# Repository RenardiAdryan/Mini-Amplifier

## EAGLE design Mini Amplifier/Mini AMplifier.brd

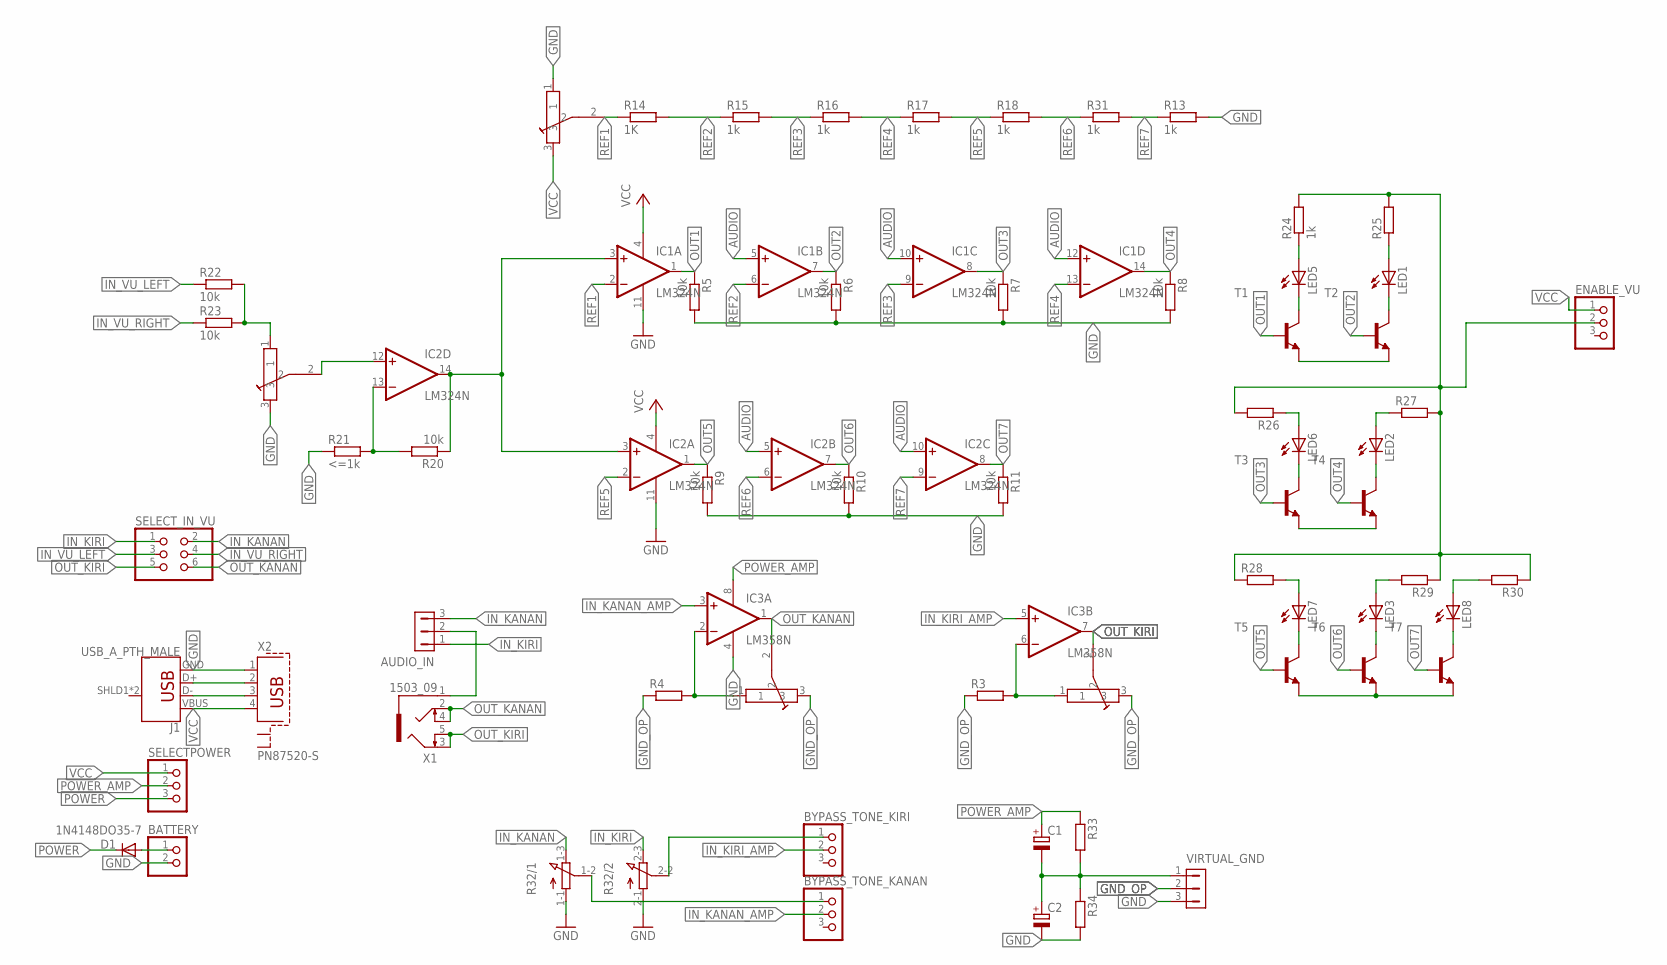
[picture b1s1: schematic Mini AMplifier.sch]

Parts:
AUDIO_IN: HDR-1X3; SIP-100-3V
BATTERY: PINHD-1X2; 1X02
BYPASS_TONE_KANAN: PINHD-1X3; 1X03
BYPASS_TONE_KIRI: PINHD-1X3; 1X03
C1, C2: CPOL-EUE2.5-6; E2,5-6
D1: 1N4148DO35-7; DO35-7
ENABLE_VU: PINHD-1X3; 1X03
IC1, IC2: LM324N; DIL14
IC3: LM358N; DIL08
J1: USB_A_PTH_MALE; USB-A-H
LED1, LED2, LED3, LED5, LED6, LED7, LED8: LED3MM
R3, R4, R25, R26, R27, R28, R29, R30: R; R0805
R5, R6, R7, R8, R9, R10, R11: 10k; 0204/7
R13, R15, R16, R17, R18, R31: 1k; 0204/7
R14: 1K; 0204/7
R20, R22, R23: 10k; R0805
R21: <=1k; R0805
R24: 1k; R0805
R32: 3RP/1610G
R33, R34: R0204/7; 0204/7
SELECTPOWER: PINHD-1X3; 1X03
SELECT_IN_VU: PINHD-2X3; 2X03
T1, T2, T3, T4, T5, T6, T7: -NPN-TO92-EBC; TO92-EBC
U$1, U$2, U$3, U$4: TRIMPOT
VIRTUAL_GND: HDR-1X3; SIP-100-3V
X1: 1503_09
X2: PN87520-S

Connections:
AUDIO: IC1.3 (+IN), IC1.5 (+IN), IC1.10 (+IN), IC1.12 (+IN), IC2.3 (+IN), IC2.5 (+IN), IC2.10 (+IN), IC2.14 (OUT), R20.1
GND: BATTERY.2, C2.-, IC1.11 (V-), IC2.11 (V-), IC3.4 (V-), J1.GND, R5.2, R6.2, R7.2, R8.2, R9.2, R10.2, R11.2, R13.2, R21.1, R32.1-1 (A), R32.2-1 (A), R34.2, T1.E, T2.E, T3.E, T4.E, T5.E, T6.E, T7.E, U$1.3, U$2.1, VIRTUAL_GND.3, X2.1
GND_OP: R3.1, R4.1, U$3.3, U$4.3, VIRTUAL_GND.2
IN_KANAN: AUDIO_IN.3, R32.1-3 (E), SELECT_IN_VU.2
IN_KANAN_AMP: BYPASS_TONE_KANAN.2, IC3.3 (+IN)
IN_KIRI: AUDIO_IN.1, R32.2-3 (E), SELECT_IN_VU.1
IN_KIRI_AMP: BYPASS_TONE_KIRI.2, IC3.5 (+IN)
IN_VU_LEFT: R22.1, SELECT_IN_VU.3
IN_VU_RIGHT: R23.1, SELECT_IN_VU.4
LAMPU: ENABLE_VU.2, R24.2, R25.2, R26.2, R27.2, R28.1, R29.1, R30.1
unnamed: AUDIO_IN.2, X1.1
unnamed: LED5.K (C), T1.C
unnamed: IC3.6 (-IN), R3.2, U$4.1
unnamed: IC3.2 (-IN), R4.2, U$3.1
unnamed: LED1.K (C), T2.C
unnamed: IC2.12 (+IN), U$1.2
unnamed: LED6.K (C), T3.C
unnamed: LED2.K (C), T4.C
unnamed: IC2.13 (-IN), R20.2, R21.2
unnamed: LED7.A, R28.2
unnamed: LED3.K (C), T6.C
unnamed: LED7.K (C), T5.C
unnamed: LED8.K (C), T7.C
unnamed: R22.2, R23.2, U$1.1
unnamed: LED3.A, R29.2
unnamed: LED8.A, R30.2
unnamed: LED6.A, R26.1
unnamed: LED2.A, R27.1
unnamed: LED5.A, R24.1
unnamed: LED1.A, R25.1
unnamed: BATTERY.1, D1.A
unnamed: J1.D+, X2.2
unnamed: J1.D-, X2.3
unnamed: C1.-, C2.+, R33.2, R34.1, VIRTUAL_GND.1
unnamed: BYPASS_TONE_KANAN.1, R32.1-2 (S)
unnamed: BYPASS_TONE_KIRI.1, R32.2-2 (S)
OUT1: IC1.1 (OUT), R5.1, T1.B
OUT2: IC1.7 (OUT), R6.1, T2.B
OUT3: IC1.8 (OUT), R7.1, T3.B
OUT4: IC1.14 (OUT), R8.1, T4.B
OUT5: IC2.1 (OUT), R9.1, T5.B
OUT6: IC2.7 (OUT), R10.1, T6.B
OUT7: IC2.8 (OUT), R11.1, T7.B
OUT_KANAN: IC3.1 (OUT), SELECT_IN_VU.6, U$3.2, X1.2, X1.4
OUT_KIRI: IC3.7 (OUT), SELECT_IN_VU.5, U$4.2, X1.3, X1.5
POWER: D1.C, SELECTPOWER.3
POWER_AMP: C1.+, IC3.8 (V+), R33.1, SELECTPOWER.2
REF1: IC1.2 (-IN), R14.1, U$2.2
REF2: IC1.6 (-IN), R14.2, R15.1
REF3: IC1.9 (-IN), R15.2, R16.1
REF4: IC1.13 (-IN), R16.2, R17.1
REF5: IC2.2 (-IN), R17.2, R18.1
REF6: IC2.6 (-IN), R18.2, R31.1
REF7: IC2.9 (-IN), R13.1, R31.2
VCC: ENABLE_VU.1, IC1.4 (V+), IC2.4 (V+), J1.VBUS, SELECTPOWER.1, U$2.3, X2.4

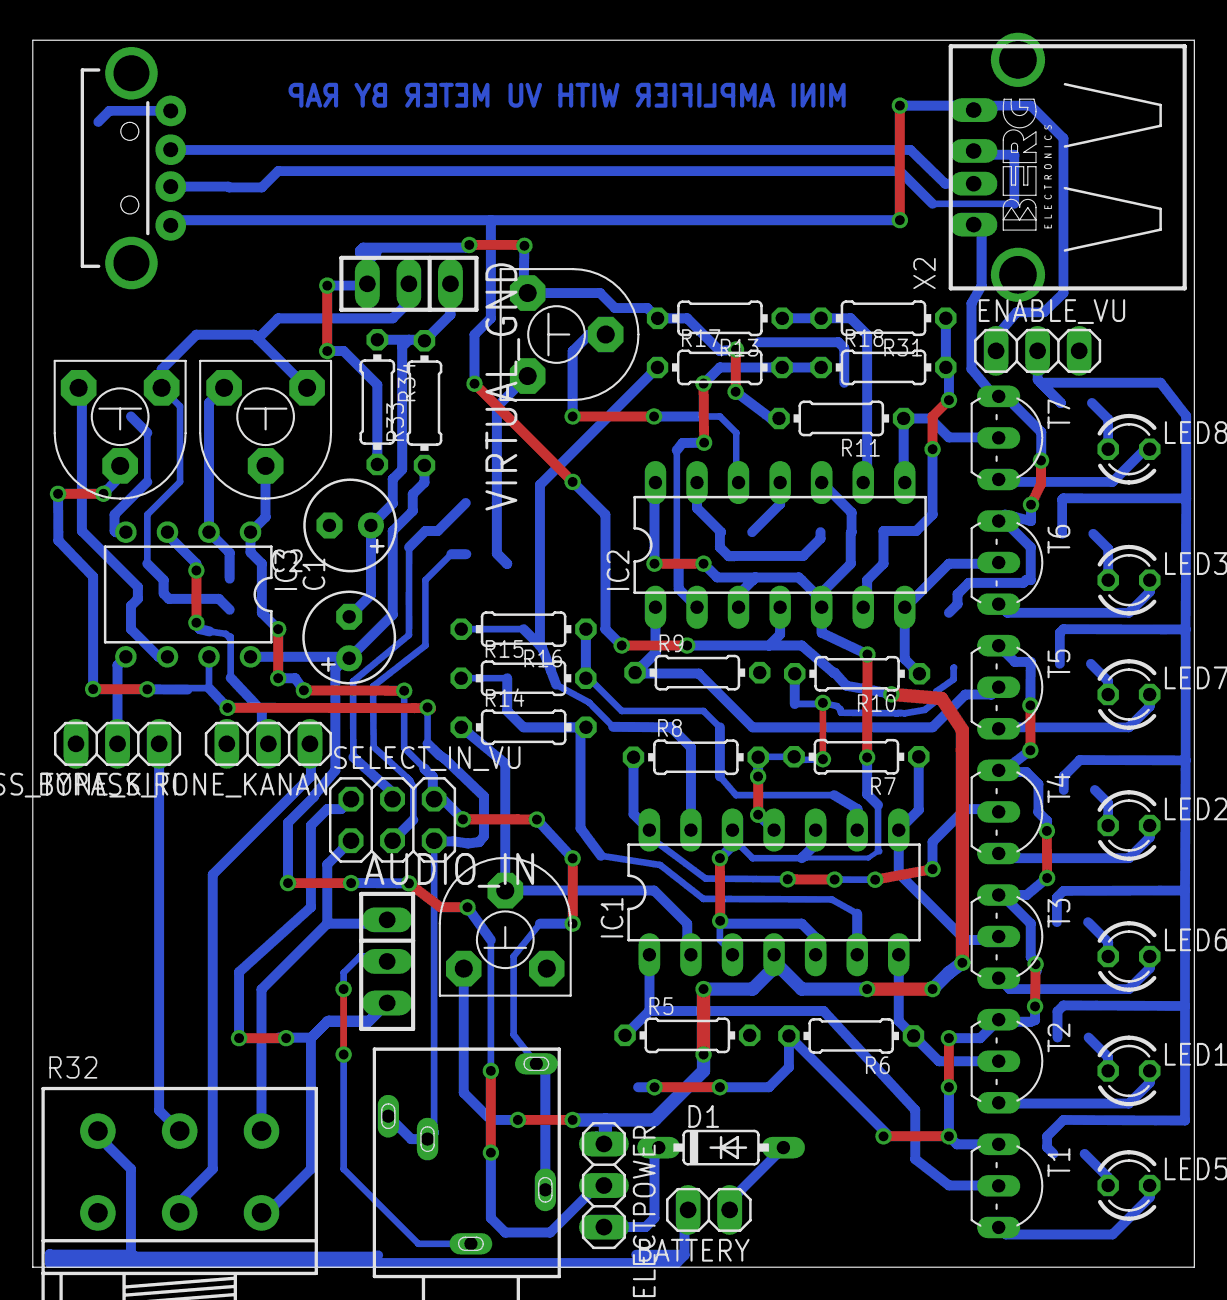
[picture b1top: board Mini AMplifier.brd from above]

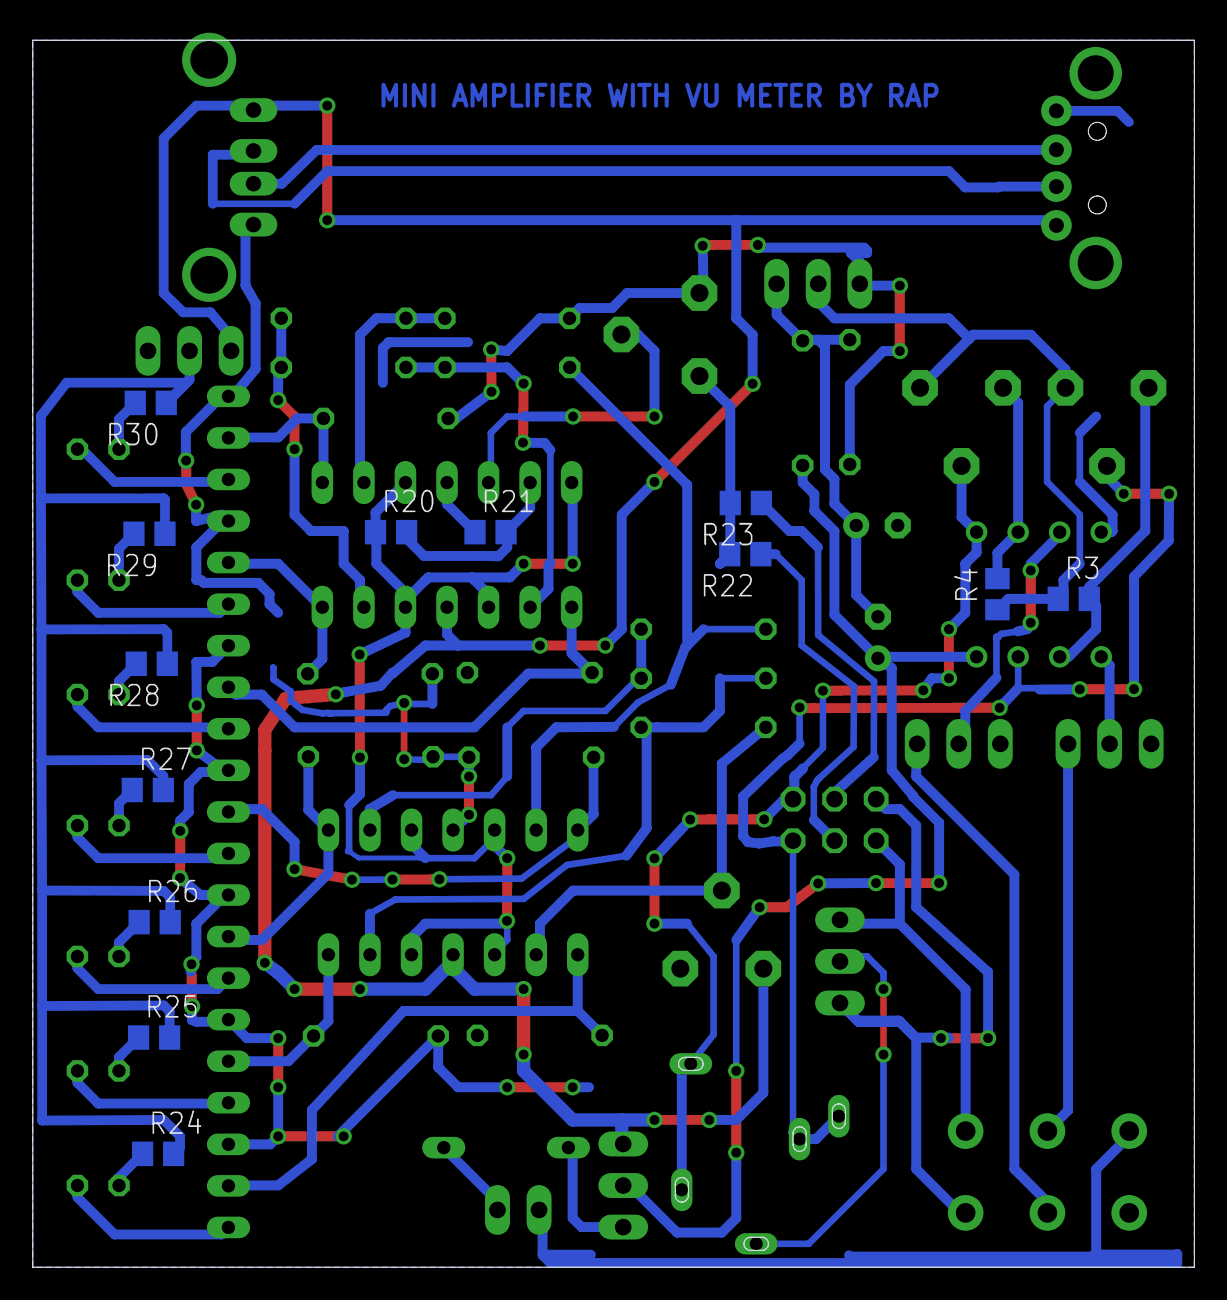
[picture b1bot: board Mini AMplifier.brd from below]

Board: 2 copper layers, 71.0 x 75.0 mm, 65 parts (13 on the bottom side), 55 nets.

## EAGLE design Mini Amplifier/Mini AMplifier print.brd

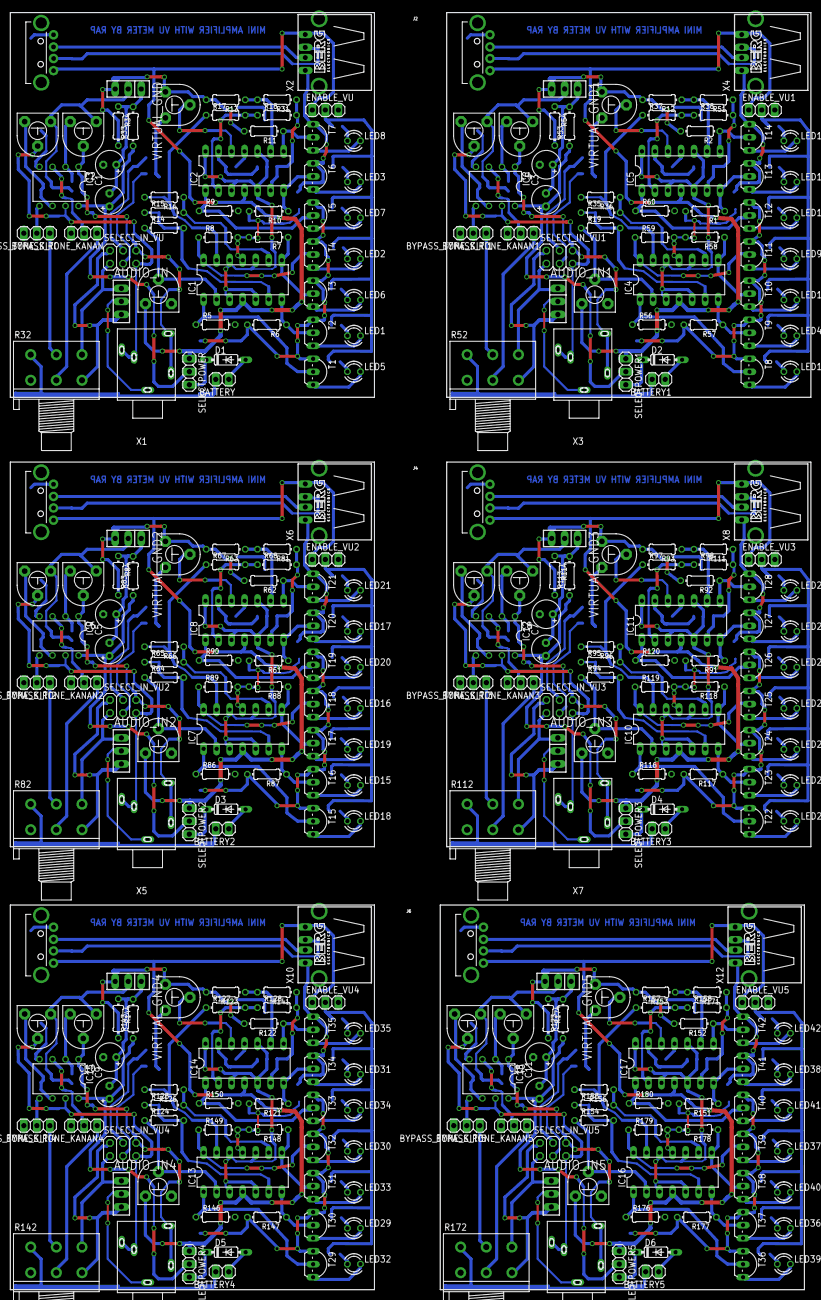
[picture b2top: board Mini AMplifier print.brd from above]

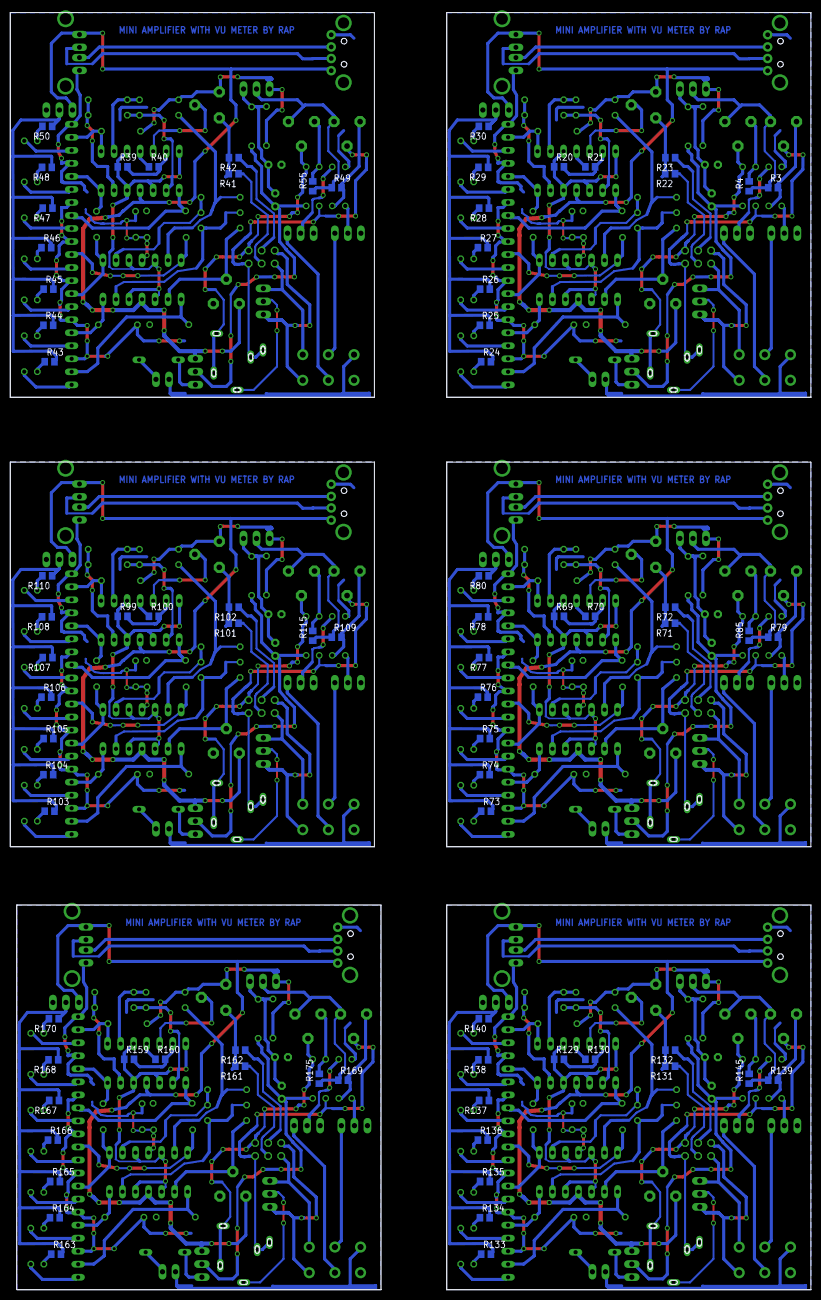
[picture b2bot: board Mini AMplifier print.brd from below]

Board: 2 copper layers, 156.1 x 249.0 mm, 390 parts (78 on the bottom side), 330 nets.

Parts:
AUDIO_IN, AUDIO_IN1, AUDIO_IN2, AUDIO_IN3, AUDIO_IN4, AUDIO_IN5: SIP-100-3V
BATTERY, BATTERY1, BATTERY2, BATTERY3, BATTERY4, BATTERY5: 1X02
BYPASS_TONE_KANAN, BYPASS_TONE_KANAN1, BYPASS_TONE_KANAN2, BYPASS_TONE_KANAN3, BYPASS_TONE_KANAN4, BYPASS_TONE_KANAN5: 1X03
BYPASS_TONE_KIRI, BYPASS_TONE_KIRI1, BYPASS_TONE_KIRI2, BYPASS_TONE_KIRI3, BYPASS_TONE_KIRI4, BYPASS_TONE_KIRI5: 1X03
C1, C2, C3, C4, C5, C6, C7, C8, C9, C10, C11, C12: E2,5-6
D1, D2, D3, D4, D5, D6: 1N4148DO35-7; DO35-7
ENABLE_VU, ENABLE_VU1, ENABLE_VU2, ENABLE_VU3, ENABLE_VU4, ENABLE_VU5: 1X03
IC1, IC2, IC4, IC5, IC7, IC8, IC10, IC11, IC13, IC14, IC16, IC17: LM324N; DIL14
IC3, IC6, IC9, IC12, IC15, IC18: LM358N; DIL08
J1, J2, J3, J4, J5, J6: USB_A_PTH_MALE; USB-A-H
LED1, LED2, LED3, LED4, LED5, LED6, LED7, LED8, LED9, LED10, LED11, LED12, LED13, LED14, LED15, LED16, LED17, LED18, LED19, LED20, LED21, LED22, LED23, LED24, LED25, LED26, LED27, LED28, LED29, LED30, LED31, LED32, LED33, LED34, LED35, LED36, LED37, LED38, LED39, LED40, LED41, LED42: LED3MM
R1, R2, R5, R6, R7, R8, R9, R10, R11, R12, R13, R14, R15, R16, R17, R18, R19, R31, R33, R34, R35, R36, R37, R38, R51, R53, R54, R56, R57, R58, R59, R60, R61, R62, R63, R64, R65, R66, R67, R68, R81, R83, R84, R86, R87, R88, R89, R90, R91, R92, R93, R94, R95, R96, R97, R98, R111, R113, R114, R116, R117, R118, R119, R120, R121, R122, R123, R124, R125, R126, R127, R128, R141, R143, R144, R146, R147, R148, R149, R150, R151, R152, R153, R154, R155, R156, R157, R158, R171, R173, R174, R176, R177, R178, R179, R180: 0204/7
R3, R4, R25, R26, R27, R28, R29, R30, R44, R45, R46, R47, R48, R49, R50, R55, R74, R75, R76, R77, R78, R79, R80, R85, R104, R105, R106, R107, R108, R109, R110, R115, R134, R135, R136, R137, R138, R139, R140, R145, R164, R165, R166, R167, R168, R169, R170, R175: R0805
R20, R22, R23, R39, R41, R42, R69, R71, R72, R99, R101, R102, R129, R131, R132, R159, R161, R162: 10k; R0805
R21, R40, R70, R100, R130, R160: <=1k; R0805
R24, R43, R73, R103, R133, R163: 1k; R0805
R32, R52, R82, R112, R142, R172: 3RP/1610G
SELECTPOWER, SELECTPOWER1, SELECTPOWER2, SELECTPOWER3, SELECTPOWER4, SELECTPOWER5: 1X03
SELECT_IN_VU, SELECT_IN_VU1, SELECT_IN_VU2, SELECT_IN_VU3, SELECT_IN_VU4, SELECT_IN_VU5: 2X03
T1, T2, T3, T4, T5, T6, T7, T8, T9, T10, T11, T12, T13, T14, T15, T16, T17, T18, T19, T20, T21, T22, T23, T24, T25, T26, T27, T28, T29, T30, T31, T32, T33, T34, T35, T36, T37, T38, T39, T40, T41, T42: TO92-EBC
U$1, U$2, U$3, U$4, U$5, U$6, U$7, U$8, U$9, U$10, U$11, U$12, U$13, U$14, U$15, U$16, U$17, U$18, U$19, U$20, U$21, U$22, U$23, U$24: TRIMPOT
VIRTUAL_GND, VIRTUAL_GND1, VIRTUAL_GND2, VIRTUAL_GND3, VIRTUAL_GND4, VIRTUAL_GND5: SIP-100-3V
X1, X3, X5, X7, X9, X11: 1503_09
X2, X4, X6, X8, X10, X12: PN87520-S

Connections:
AUDIO: IC1.3, IC1.5, IC1.10, IC1.12, IC2.3, IC2.5, IC2.10, IC2.14, R20.1
AUDIO1: IC4.3, IC4.5, IC4.10, IC4.12, IC5.3, IC5.5, IC5.10, IC5.14, R39.1
AUDIO2: IC7.3, IC7.5, IC7.10, IC7.12, IC8.3, IC8.5, IC8.10, IC8.14, R69.1
AUDIO3: IC10.3, IC10.5, IC10.10, IC10.12, IC11.3, IC11.5, IC11.10, IC11.14, R99.1
AUDIO4: IC13.3, IC13.5, IC13.10, IC13.12, IC14.3, IC14.5, IC14.10, IC14.14, R129.1
AUDIO5: IC16.3, IC16.5, IC16.10, IC16.12, IC17.3, IC17.5, IC17.10, IC17.14, R159.1
GND: BATTERY.2, C2.-, IC1.11, IC2.11, IC3.4, J1.GND, R5.2, R6.2, R7.2, R8.2, R9.2, R10.2, R11.2, R13.2, R21.1, R32.1-1, R32.2-1, R34.2, T1.E, T2.E, T3.E, T4.E, T5.E, T6.E, T7.E, U$1.3, U$2.1, VIRTUAL_GND.3, X2.1
GND1: BATTERY1.2, C4.-, IC4.11, IC5.11, IC6.4, J2.GND, R1.2, R2.2, R12.2, R40.1, R52.1-1, R52.2-1, R54.2, R56.2, R57.2, R58.2, R59.2, R60.2, T8.E, T9.E, T10.E, T11.E, T12.E, T13.E, T14.E, U$5.3, U$6.1, VIRTUAL_GND1.3, X4.1
GND2: BATTERY2.2, C6.-, IC7.11, IC8.11, IC9.4, J3.GND, R61.2, R62.2, R63.2, R70.1, R82.1-1, R82.2-1, R84.2, R86.2, R87.2, R88.2, R89.2, R90.2, T15.E, T16.E, T17.E, T18.E, T19.E, T20.E, T21.E, U$9.3, U$10.1, VIRTUAL_GND2.3, X6.1
GND3: BATTERY3.2, C8.-, IC10.11, IC11.11, IC12.4, J4.GND, R91.2, R92.2, R93.2, R100.1, R112.1-1, R112.2-1, R114.2, R116.2, R117.2, R118.2, R119.2, R120.2, T22.E, T23.E, T24.E, T25.E, T26.E, T27.E, T28.E, U$13.3, U$14.1, VIRTUAL_GND3.3, X8.1
GND4: BATTERY4.2, C10.-, IC13.11, IC14.11, IC15.4, J5.GND, R121.2, R122.2, R123.2, R130.1, R142.1-1, R142.2-1, R144.2, R146.2, R147.2, R148.2, R149.2, R150.2, T29.E, T30.E, T31.E, T32.E, T33.E, T34.E, T35.E, U$17.3, U$18.1, VIRTUAL_GND4.3, X10.1
GND5: BATTERY5.2, C12.-, IC16.11, IC17.11, IC18.4, J6.GND, R151.2, R152.2, R153.2, R160.1, R172.1-1, R172.2-1, R174.2, R176.2, R177.2, R178.2, R179.2, R180.2, T36.E, T37.E, T38.E, T39.E, T40.E, T41.E, T42.E, U$21.3, U$22.1, VIRTUAL_GND5.3, X12.1
GND_OP: R3.1, R4.1, U$3.3, U$4.3, VIRTUAL_GND.2
GND_OP1: R49.1, R55.1, U$7.3, U$8.3, VIRTUAL_GND1.2
GND_OP2: R79.1, R85.1, U$11.3, U$12.3, VIRTUAL_GND2.2
GND_OP3: R109.1, R115.1, U$15.3, U$16.3, VIRTUAL_GND3.2
GND_OP4: R139.1, R145.1, U$19.3, U$20.3, VIRTUAL_GND4.2
GND_OP5: R169.1, R175.1, U$23.3, U$24.3, VIRTUAL_GND5.2
IN_KANAN: AUDIO_IN.3, R32.1-3, SELECT_IN_VU.2
IN_KANAN1: AUDIO_IN1.3, R52.1-3, SELECT_IN_VU1.2
IN_KANAN2: AUDIO_IN2.3, R82.1-3, SELECT_IN_VU2.2
IN_KANAN3: AUDIO_IN3.3, R112.1-3, SELECT_IN_VU3.2
IN_KANAN4: AUDIO_IN4.3, R142.1-3, SELECT_IN_VU4.2
IN_KANAN5: AUDIO_IN5.3, R172.1-3, SELECT_IN_VU5.2
IN_KANAN_AMP: BYPASS_TONE_KANAN.2, IC3.3
IN_KANAN_AMP1: BYPASS_TONE_KANAN1.2, IC6.3
IN_KANAN_AMP2: BYPASS_TONE_KANAN2.2, IC9.3
IN_KANAN_AMP3: BYPASS_TONE_KANAN3.2, IC12.3
IN_KANAN_AMP4: BYPASS_TONE_KANAN4.2, IC15.3
IN_KANAN_AMP5: BYPASS_TONE_KANAN5.2, IC18.3
IN_KIRI: AUDIO_IN.1, R32.2-3, SELECT_IN_VU.1
IN_KIRI1: AUDIO_IN1.1, R52.2-3, SELECT_IN_VU1.1
IN_KIRI2: AUDIO_IN2.1, R82.2-3, SELECT_IN_VU2.1
IN_KIRI3: AUDIO_IN3.1, R112.2-3, SELECT_IN_VU3.1
IN_KIRI4: AUDIO_IN4.1, R142.2-3, SELECT_IN_VU4.1
IN_KIRI5: AUDIO_IN5.1, R172.2-3, SELECT_IN_VU5.1
IN_KIRI_AMP: BYPASS_TONE_KIRI.2, IC3.5
IN_KIRI_AMP1: BYPASS_TONE_KIRI1.2, IC6.5
IN_KIRI_AMP2: BYPASS_TONE_KIRI2.2, IC9.5
IN_KIRI_AMP3: BYPASS_TONE_KIRI3.2, IC12.5
IN_KIRI_AMP4: BYPASS_TONE_KIRI4.2, IC15.5
IN_KIRI_AMP5: BYPASS_TONE_KIRI5.2, IC18.5
IN_VU_LEFT: R22.1, SELECT_IN_VU.3
IN_VU_LEFT1: R41.1, SELECT_IN_VU1.3
IN_VU_LEFT2: R71.1, SELECT_IN_VU2.3
IN_VU_LEFT3: R101.1, SELECT_IN_VU3.3
IN_VU_LEFT4: R131.1, SELECT_IN_VU4.3
IN_VU_LEFT5: R161.1, SELECT_IN_VU5.3
IN_VU_RIGHT: R23.1, SELECT_IN_VU.4
IN_VU_RIGHT1: R42.1, SELECT_IN_VU1.4
IN_VU_RIGHT2: R72.1, SELECT_IN_VU2.4
IN_VU_RIGHT3: R102.1, SELECT_IN_VU3.4
IN_VU_RIGHT4: R132.1, SELECT_IN_VU4.4
IN_VU_RIGHT5: R162.1, SELECT_IN_VU5.4
LAMPU: ENABLE_VU.2, R24.2, R25.2, R26.2, R27.2, R28.1, R29.1, R30.1
LAMPU1: ENABLE_VU1.2, R43.2, R44.2, R45.2, R46.2, R47.1, R48.1, R50.1
LAMPU2: ENABLE_VU2.2, R73.2, R74.2, R75.2, R76.2, R77.1, R78.1, R80.1
LAMPU3: ENABLE_VU3.2, R103.2, R104.2, R105.2, R106.2, R107.1, R108.1, R110.1
LAMPU4: ENABLE_VU4.2, R133.2, R134.2, R135.2, R136.2, R137.1, R138.1, R140.1
LAMPU5: ENABLE_VU5.2, R163.2, R164.2, R165.2, R166.2, R167.1, R168.1, R170.1
unnamed: AUDIO_IN.2, X1.1
unnamed: LED5.K, T1.C
unnamed: IC3.6, R3.2, U$4.1
unnamed: IC3.2, R4.2, U$3.1
unnamed: LED1.K, T2.C
unnamed: IC2.12, U$1.2
unnamed: LED6.K, T3.C
unnamed: LED2.K, T4.C
unnamed: IC2.13, R20.2, R21.2
unnamed: LED7.A, R28.2
unnamed: LED3.K, T6.C
unnamed: LED7.K, T5.C
unnamed: LED8.K, T7.C
unnamed: R22.2, R23.2, U$1.1
unnamed: LED3.A, R29.2
unnamed: LED8.A, R30.2
unnamed: LED6.A, R26.1
unnamed: LED2.A, R27.1
unnamed: LED5.A, R24.1
unnamed: LED1.A, R25.1
unnamed: BATTERY.1, D1.A
unnamed: J1.D+, X2.2
unnamed: J1.D-, X2.3
unnamed: C1.-, C2.+, R33.2, R34.1, VIRTUAL_GND.1
unnamed: IC6.6, R49.2, U$8.1
unnamed: BYPASS_TONE_KANAN.1, R32.1-2
unnamed: BYPASS_TONE_KIRI.1, R32.2-2
unnamed: IC6.2, R55.2, U$7.1
unnamed: LED11.K, T8.C
unnamed: LED4.K, T9.C
unnamed: LED12.K, T10.C
unnamed: LED9.K, T11.C
unnamed: LED10.K, T13.C
unnamed: LED13.K, T12.C
unnamed: LED14.K, T14.C
unnamed: IC5.12, U$5.2
unnamed: IC5.13, R39.2, R40.2
unnamed: R41.2, R42.2, U$5.1
unnamed: AUDIO_IN1.2, X3.1
unnamed: LED13.A, R47.2
unnamed: LED10.A, R48.2
unnamed: LED14.A, R50.2
unnamed: LED12.A, R45.1
unnamed: LED9.A, R46.1
unnamed: LED11.A, R43.1
unnamed: LED4.A, R44.1
unnamed: J2.D+, X4.2
unnamed: J2.D-, X4.3
unnamed: BATTERY1.1, D2.A
unnamed: C3.-, C4.+, R53.2, R54.1, VIRTUAL_GND1.1
unnamed: BYPASS_TONE_KANAN1.1, R52.1-2
unnamed: BYPASS_TONE_KIRI1.1, R52.2-2
unnamed: IC9.6, R79.2, U$12.1
unnamed: IC9.2, R85.2, U$11.1
unnamed: LED18.K, T15.C
unnamed: LED15.K, T16.C
unnamed: LED19.K, T17.C
unnamed: LED16.K, T18.C
unnamed: LED17.K, T20.C
unnamed: LED20.K, T19.C
unnamed: LED21.K, T21.C
unnamed: IC8.12, U$9.2
unnamed: IC8.13, R69.2, R70.2
unnamed: R71.2, R72.2, U$9.1
unnamed: AUDIO_IN2.2, X5.1
unnamed: LED20.A, R77.2
unnamed: LED17.A, R78.2
unnamed: LED21.A, R80.2
unnamed: LED19.A, R75.1
unnamed: LED16.A, R76.1
unnamed: LED18.A, R73.1
unnamed: LED15.A, R74.1
unnamed: J3.D+, X6.2
unnamed: J3.D-, X6.3
unnamed: BATTERY2.1, D3.A
unnamed: C5.-, C6.+, R83.2, R84.1, VIRTUAL_GND2.1
unnamed: BYPASS_TONE_KANAN2.1, R82.1-2
unnamed: BYPASS_TONE_KIRI2.1, R82.2-2
unnamed: IC12.6, R109.2, U$16.1
unnamed: IC12.2, R115.2, U$15.1
unnamed: LED25.K, T22.C
unnamed: LED22.K, T23.C
unnamed: LED26.K, T24.C
unnamed: LED23.K, T25.C
unnamed: LED24.K, T27.C
unnamed: LED27.K, T26.C
unnamed: LED28.K, T28.C
unnamed: IC11.12, U$13.2
unnamed: IC11.13, R99.2, R100.2
unnamed: R101.2, R102.2, U$13.1
unnamed: AUDIO_IN3.2, X7.1
unnamed: LED27.A, R107.2
unnamed: LED24.A, R108.2
unnamed: LED28.A, R110.2
unnamed: LED26.A, R105.1
unnamed: LED23.A, R106.1
unnamed: LED25.A, R103.1
unnamed: LED22.A, R104.1
unnamed: J4.D+, X8.2
unnamed: J4.D-, X8.3
unnamed: BATTERY3.1, D4.A
unnamed: C7.-, C8.+, R113.2, R114.1, VIRTUAL_GND3.1
unnamed: BYPASS_TONE_KANAN3.1, R112.1-2
unnamed: BYPASS_TONE_KIRI3.1, R112.2-2
unnamed: IC15.6, R139.2, U$20.1
unnamed: IC15.2, R145.2, U$19.1
unnamed: LED32.K, T29.C
unnamed: LED29.K, T30.C
unnamed: LED33.K, T31.C
unnamed: LED30.K, T32.C
unnamed: LED31.K, T34.C
unnamed: LED34.K, T33.C
unnamed: LED35.K, T35.C
unnamed: IC14.12, U$17.2
unnamed: IC14.13, R129.2, R130.2
unnamed: R131.2, R132.2, U$17.1
unnamed: AUDIO_IN4.2, X9.1
unnamed: LED34.A, R137.2
unnamed: LED31.A, R138.2
unnamed: LED35.A, R140.2
unnamed: LED33.A, R135.1
unnamed: LED30.A, R136.1
unnamed: LED32.A, R133.1
unnamed: LED29.A, R134.1
unnamed: J5.D+, X10.2
unnamed: J5.D-, X10.3
unnamed: BATTERY4.1, D5.A
unnamed: C9.-, C10.+, R143.2, R144.1, VIRTUAL_GND4.1
unnamed: BYPASS_TONE_KANAN4.1, R142.1-2
unnamed: BYPASS_TONE_KIRI4.1, R142.2-2
unnamed: IC18.6, R169.2, U$24.1
unnamed: IC18.2, R175.2, U$23.1
unnamed: LED39.K, T36.C
unnamed: LED36.K, T37.C
unnamed: LED40.K, T38.C
unnamed: LED37.K, T39.C
unnamed: LED38.K, T41.C
unnamed: LED41.K, T40.C
unnamed: LED42.K, T42.C
unnamed: IC17.12, U$21.2
unnamed: IC17.13, R159.2, R160.2
unnamed: R161.2, R162.2, U$21.1
unnamed: AUDIO_IN5.2, X11.1
unnamed: LED41.A, R167.2
unnamed: LED38.A, R168.2
unnamed: LED42.A, R170.2
unnamed: LED40.A, R165.1
unnamed: LED37.A, R166.1
unnamed: LED39.A, R163.1
unnamed: LED36.A, R164.1
unnamed: J6.D+, X12.2
unnamed: J6.D-, X12.3
unnamed: BATTERY5.1, D6.A
unnamed: C11.-, C12.+, R173.2, R174.1, VIRTUAL_GND5.1
unnamed: BYPASS_TONE_KANAN5.1, R172.1-2
unnamed: BYPASS_TONE_KIRI5.1, R172.2-2
OUT1: IC1.1, R5.1, T1.B
OUT2: IC1.7, R6.1, T2.B
OUT3: IC1.8, R7.1, T3.B
OUT4: IC1.14, R8.1, T4.B
OUT5: IC2.1, R9.1, T5.B
OUT6: IC2.7, R10.1, T6.B
OUT7: IC2.8, R11.1, T7.B
OUT8: IC4.1, R56.1, T8.B
OUT9: IC4.7, R57.1, T9.B
OUT10: IC4.8, R58.1, T10.B
OUT11: IC4.14, R59.1, T11.B
OUT12: IC5.8, R2.1, T14.B
OUT13: IC5.7, R1.1, T13.B
OUT14: IC5.1, R60.1, T12.B
OUT15: IC7.1, R86.1, T15.B
OUT16: IC7.7, R87.1, T16.B
OUT17: IC7.8, R88.1, T17.B
OUT18: IC7.14, R89.1, T18.B
OUT19: IC8.8, R62.1, T21.B
OUT20: IC8.7, R61.1, T20.B
OUT21: IC8.1, R90.1, T19.B
OUT22: IC10.1, R116.1, T22.B
OUT23: IC10.7, R117.1, T23.B
OUT24: IC10.8, R118.1, T24.B
OUT25: IC10.14, R119.1, T25.B
OUT26: IC11.8, R92.1, T28.B
OUT27: IC11.7, R91.1, T27.B
OUT28: IC11.1, R120.1, T26.B
OUT29: IC13.1, R146.1, T29.B
OUT30: IC13.7, R147.1, T30.B
OUT31: IC13.8, R148.1, T31.B
OUT32: IC13.14, R149.1, T32.B
OUT33: IC14.8, R122.1, T35.B
OUT34: IC14.7, R121.1, T34.B
OUT35: IC14.1, R150.1, T33.B
OUT36: IC16.1, R176.1, T36.B
OUT37: IC16.7, R177.1, T37.B
OUT38: IC16.8, R178.1, T38.B
OUT39: IC16.14, R179.1, T39.B
OUT40: IC17.8, R152.1, T42.B
OUT41: IC17.7, R151.1, T41.B
OUT42: IC17.1, R180.1, T40.B
OUT_KANAN: IC3.1, SELECT_IN_VU.6, U$3.2, X1.2, X1.4
OUT_KANAN1: IC6.1, SELECT_IN_VU1.6, U$7.2, X3.2, X3.4
OUT_KANAN2: IC9.1, SELECT_IN_VU2.6, U$11.2, X5.2, X5.4
OUT_KANAN3: IC12.1, SELECT_IN_VU3.6, U$15.2, X7.2, X7.4
OUT_KANAN4: IC15.1, SELECT_IN_VU4.6, U$19.2, X9.2, X9.4
OUT_KANAN5: IC18.1, SELECT_IN_VU5.6, U$23.2, X11.2, X11.4
OUT_KIRI: IC3.7, SELECT_IN_VU.5, U$4.2, X1.3, X1.5
OUT_KIRI1: IC6.7, SELECT_IN_VU1.5, U$8.2, X3.3, X3.5
OUT_KIRI2: IC9.7, SELECT_IN_VU2.5, U$12.2, X5.3, X5.5
OUT_KIRI3: IC12.7, SELECT_IN_VU3.5, U$16.2, X7.3, X7.5
OUT_KIRI4: IC15.7, SELECT_IN_VU4.5, U$20.2, X9.3, X9.5
OUT_KIRI5: IC18.7, SELECT_IN_VU5.5, U$24.2, X11.3, X11.5
POWER: D1.C, SELECTPOWER.3
POWER1: D2.C, SELECTPOWER1.3
POWER2: D3.C, SELECTPOWER2.3
POWER3: D4.C, SELECTPOWER3.3
POWER4: D5.C, SELECTPOWER4.3
POWER5: D6.C, SELECTPOWER5.3
POWER_AMP: C1.+, IC3.8, R33.1, SELECTPOWER.2
POWER_AMP1: C3.+, IC6.8, R53.1, SELECTPOWER1.2
POWER_AMP2: C5.+, IC9.8, R83.1, SELECTPOWER2.2
POWER_AMP3: C7.+, IC12.8, R113.1, SELECTPOWER3.2
POWER_AMP4: C9.+, IC15.8, R143.1, SELECTPOWER4.2
POWER_AMP5: C11.+, IC18.8, R173.1, SELECTPOWER5.2
REF1: IC1.2, R14.1, U$2.2
REF2: IC1.6, R14.2, R15.1
REF3: IC1.9, R15.2, R16.1
REF4: IC1.13, R16.2, R17.1
REF5: IC2.2, R17.2, R18.1
REF6: IC2.6, R18.2, R31.1
REF7: IC2.9, R13.1, R31.2
REF8: IC4.2, R19.1, U$6.2
REF9: IC4.6, R19.2, R35.1
REF10: IC4.9, R35.2, R36.1
REF11: IC5.2, R37.2, R38.1
REF12: IC4.13, R36.2, R37.1
REF13: IC5.6, R38.2, R51.1
REF14: IC5.9, R12.1, R51.2
REF15: IC7.2, R64.1, U$10.2
REF16: IC7.6, R64.2, R65.1
REF17: IC7.9, R65.2, R66.1
REF18: IC8.2, R67.2, R68.1
REF19: IC7.13, R66.2, R67.1
REF20: IC8.6, R68.2, R81.1
REF21: IC8.9, R63.1, R81.2
REF22: IC10.2, R94.1, U$14.2
REF23: IC10.6, R94.2, R95.1
REF24: IC10.9, R95.2, R96.1
REF25: IC11.2, R97.2, R98.1
REF26: IC10.13, R96.2, R97.1
REF27: IC11.6, R98.2, R111.1
REF28: IC11.9, R93.1, R111.2
REF29: IC13.2, R124.1, U$18.2
REF30: IC13.6, R124.2, R125.1
REF31: IC13.9, R125.2, R126.1
REF32: IC14.2, R127.2, R128.1
REF33: IC13.13, R126.2, R127.1
REF34: IC14.6, R128.2, R141.1
REF35: IC14.9, R123.1, R141.2
REF36: IC16.2, R154.1, U$22.2
REF37: IC16.6, R154.2, R155.1
REF38: IC16.9, R155.2, R156.1
REF39: IC17.2, R157.2, R158.1
REF40: IC16.13, R156.2, R157.1
REF41: IC17.6, R158.2, R171.1
REF42: IC17.9, R153.1, R171.2
VCC: ENABLE_VU.1, IC1.4, IC2.4, J1.VBUS, SELECTPOWER.1, U$2.3, X2.4
VCC1: ENABLE_VU1.1, IC4.4, IC5.4, J2.VBUS, SELECTPOWER1.1, U$6.3, X4.4
VCC2: ENABLE_VU2.1, IC7.4, IC8.4, J3.VBUS, SELECTPOWER2.1, U$10.3, X6.4
VCC3: ENABLE_VU3.1, IC10.4, IC11.4, J4.VBUS, SELECTPOWER3.1, U$14.3, X8.4
VCC4: ENABLE_VU4.1, IC13.4, IC14.4, J5.VBUS, SELECTPOWER4.1, U$18.3, X10.4
VCC5: ENABLE_VU5.1, IC16.4, IC17.4, J6.VBUS, SELECTPOWER5.1, U$22.3, X12.4

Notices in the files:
parts and their libraries:
con-hdrs40: Copyright (C) 2004, Bob Starr (bobstarr@mindspring.com)
SparkFun-Connectors: Licensing: Creative Commons ShareAlike 4.0 International - https://creativecommons.org/licenses/by-sa/4.0
